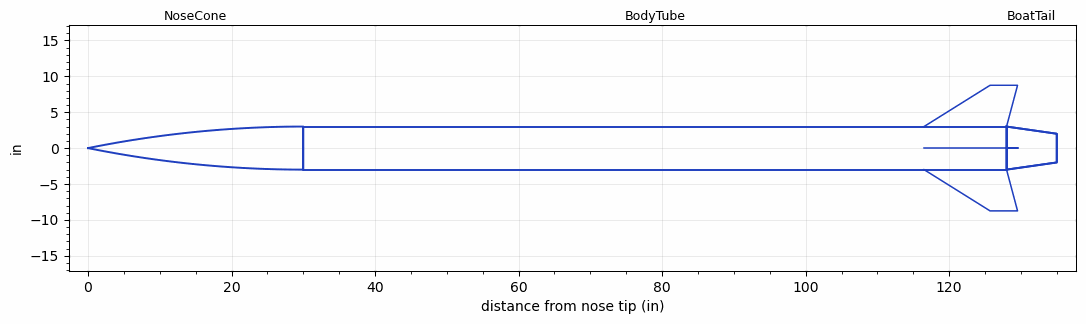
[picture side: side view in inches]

<RASAeroDocument>
 <FileVersion>2</FileVersion>
 <RocketDesign>
  <NoseCone>
   <Length>30</Length>
   <Diameter>6</Diameter>
   <Shape>Tangent Ogive</Shape>
   <Location>0</Location>
  </NoseCone>
  <BodyTube>
   <Length>98</Length>
   <Diameter>6</Diameter>
   <RailGuideDiameter>0.5</RailGuideDiameter>
   <RailGuideHeight>0.5</RailGuideHeight>
   <Location>30</Location>
   <BoattailLength>7</BoattailLength>
   <BoattailRearDiameter>4</BoattailRearDiameter>
   <Fin>
    <Count>4</Count>
    <Chord>11.5</Chord>
    <Span>5.75</Span>
    <SweepDistance>9.2</SweepDistance>
    <TipChord>3.8333</TipChord>
    <Thickness>0.25</Thickness>
    <Location>11.5</Location>
    <AirfoilSection>Hexagonal</AirfoilSection>
    <FX1>1</FX1>
    <FX3>1</FX3>
   </Fin>
  </BodyTube>
  <BoatTail>
   <Length>7</Length>
   <Diameter>6</Diameter>
   <RearDiameter>4</RearDiameter>
   <Location>128</Location>
  </BoatTail>
  <Surface>Smooth (Zero Roughness)</Surface>
  <ModifiedBarrowman>False</ModifiedBarrowman>
  <Turbulence>False</Turbulence>
  <UseBooster1>False</UseBooster1>
  <UseBooster2>False</UseBooster2>
 </RocketDesign>
 <LaunchSite>
  <Altitude>0</Altitude>
  <Pressure>0</Pressure>
  <RodAngle>0</RodAngle>
  <RodLength>4</RodLength>
  <Temperature>74</Temperature>
  <WindSpeed>0</WindSpeed>
 </LaunchSite>
 <Recovery>
  <Altitude1>1000</Altitude1>
  <Altitude2>1000</Altitude2>
  <DeviceType1>None</DeviceType1>
  <DeviceType2>None</DeviceType2>
  <Event1>False</Event1>
  <Event2>False</Event2>
  <Size1>1</Size1>
  <Size2>1</Size2>
  <EventType1>None</EventType1>
  <EventType2>None</EventType2>
  <CD1>1.33</CD1>
  <CD2>1.33</CD2>
 </Recovery>
 <SimulationList>
  <Simulation>
   <SustainerEngine>O3400-IM-P  (CTI)</SustainerEngine>
   <SustainerLaunchWt>74</SustainerLaunchWt>
   <SustainerNozzleDiameter>2.7</SustainerNozzleDiameter>
   <SustainerCG>88.4</SustainerCG>
   <SustainerIgnitionDelay>0</SustainerIgnitionDelay>
   <Booster1SeparationDelay>0</Booster1SeparationDelay>
   <Booster1IgnitionDelay>0</Booster1IgnitionDelay>
   <IncludeBooster1>False</IncludeBooster1>
   <Booster2Delay>0</Booster2Delay>
   <IncludeBooster2>False</IncludeBooster2>
   <TimetoApogee>38.07962</TimetoApogee>
   <MaxAltitude>27714.16</MaxAltitude>
   <MaxVelocity>1875.445</MaxVelocity>
  </Simulation>
 </SimulationList>
</RASAeroDocument>
